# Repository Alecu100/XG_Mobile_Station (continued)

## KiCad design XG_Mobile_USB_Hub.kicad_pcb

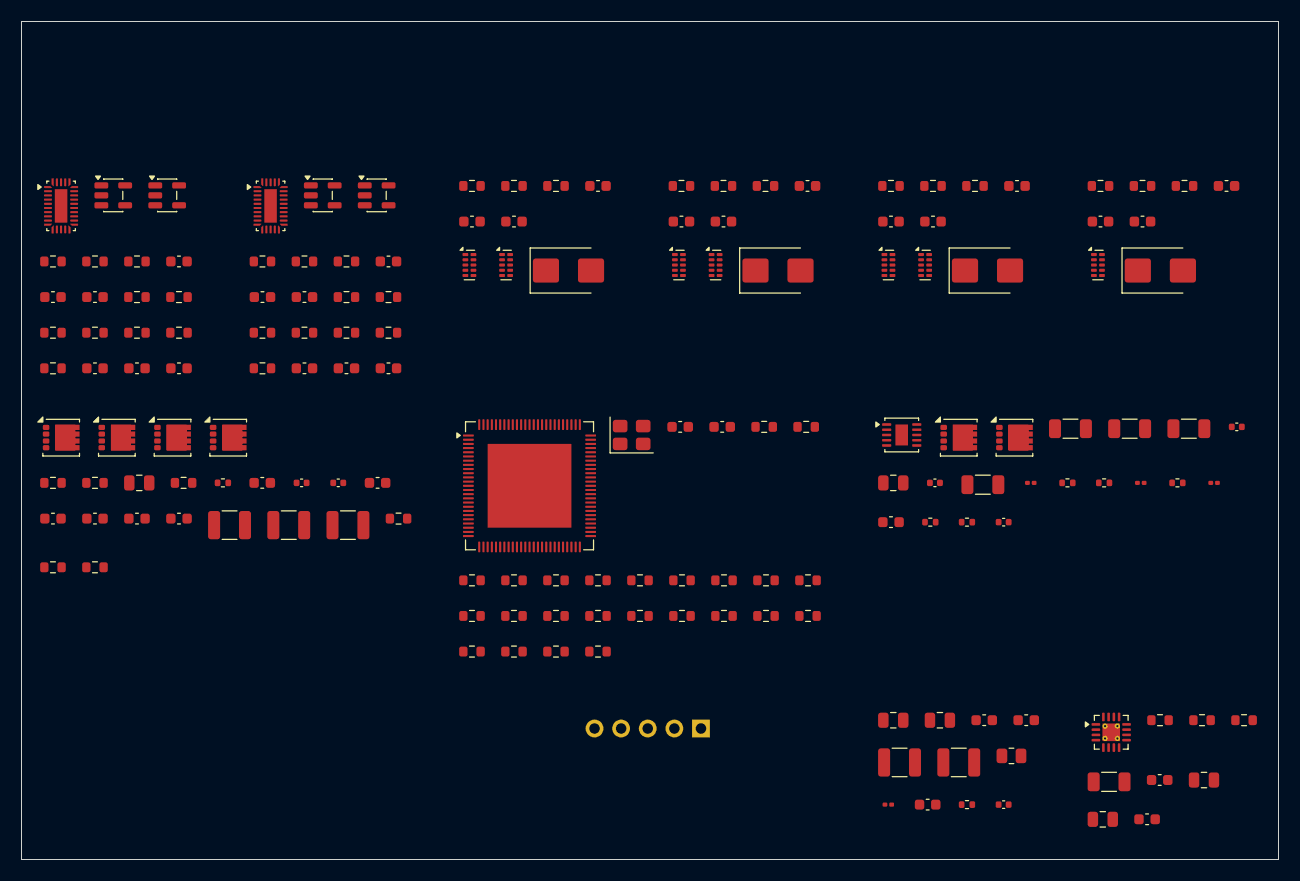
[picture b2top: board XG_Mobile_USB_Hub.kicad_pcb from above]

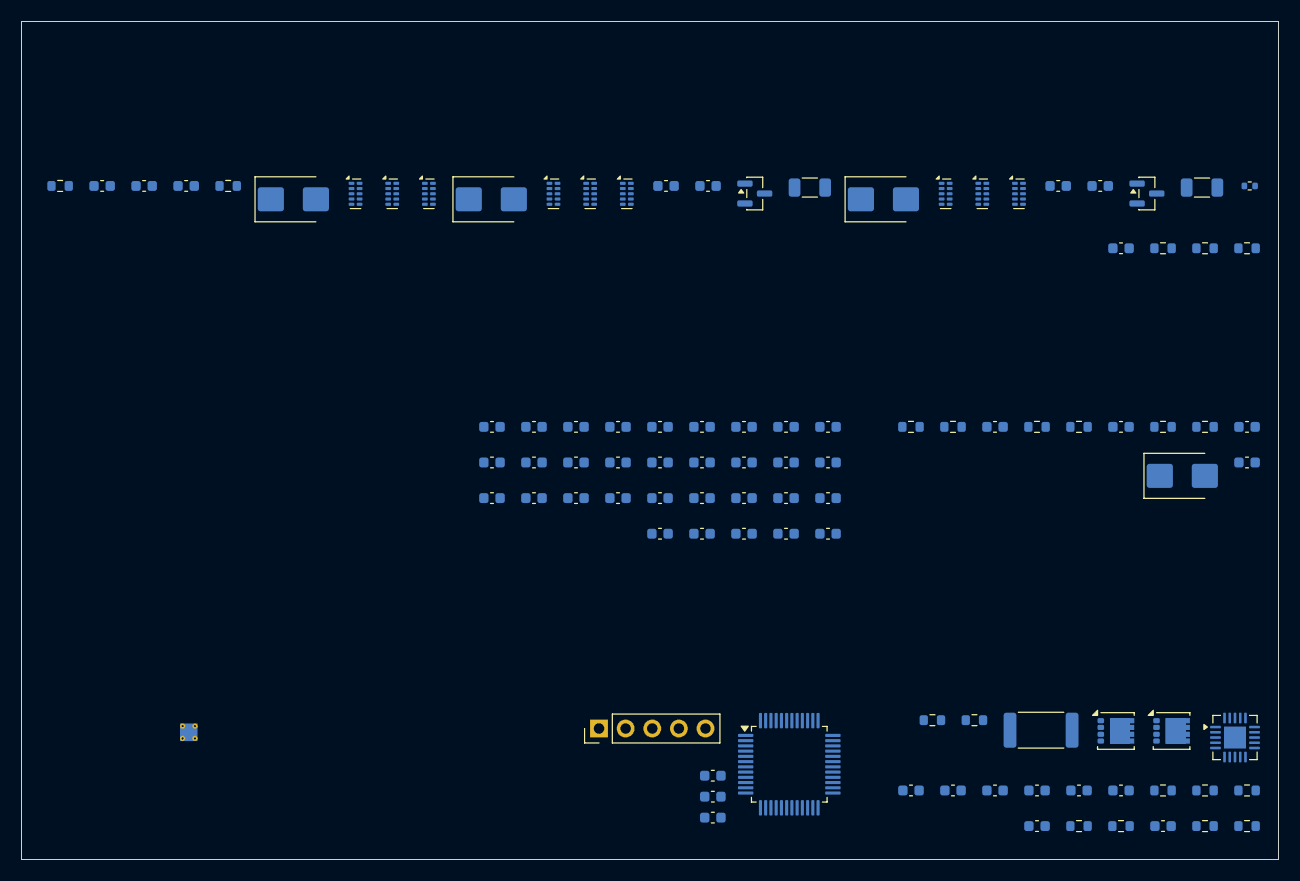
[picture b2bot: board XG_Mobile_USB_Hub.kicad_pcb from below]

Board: 4 copper layers, 120.0 x 80.0 mm, 300 parts (99 on the bottom side), 177 nets, no tracks yet.

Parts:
C101: 180pF; C_0805_2012Metric
C102: 120nF - REVIEW LOOP; C_0603_1608Metric
C103: 220pF - REVIEW LOOP; C_0402_1005Metric
C104: 33nF; C_0402_1005Metric
C105, C106: 22uF 6.3V; C_0603_1608Metric
C107, C108, C304: 100nF 16V; C_0603_1608Metric
C109, C303, C402, C1401: 100nF 25V; C_0603_1608Metric
C110: 10uF 25V; C_1210_3225Metric
C111: 27uF 25V; C111
C112: 120uF 35V; C112
C113: 120uF 35V; C113
C114, C115: 10uF 50V; C_1210_3225Metric
C201, C202, C203, C401: 10uF 25V; C_1206_3216Metric
C204: 1uF 25V; C_0402_1005Metric
C205: 2.2uF 10V; C_0805_2012Metric
C206: 100nF 16V; C_0402_1005Metric
C207: 100uF 10V; C_1206_3216Metric
C208: 3.3nF; C_0201_0603Metric
C209: 120pF; C_0201_0603Metric
C210: 4.3nF; C_0603_1608Metric
C211: 1nF; C_0402_1005Metric
C301, C302: 10uF 25V; C_0805_2012Metric
C305, C306: 15uF 16V; C_1210_3225Metric
C307: 150pF; C_0603_1608Metric
C308: 22nF; C_0402_1005Metric
C403, C404: 22uF 6.3V; C_0805_2012Metric
C405: 3.3nF; C_0603_1608Metric
C501, C502: 27pF C0G - tune CL; C_0603_1608Metric
C503, C504, C505, C506, C507, C508, C509, C510, C511, C512, C513, C514, C515, C516, C517, C518, C519, C520, C604, C605, C606, C607, C704, C705, C706, C707, C1206, C1300, C1301, C1304, C1306: 100nF; C_0603_1608Metric
C521, C522: 10uF 6.3V; C_0603_1608Metric
C523, C524, C525, C526, C527, C528, C529, C530, C531, C532, C533, C534: 220nF 10V; C_0603_1608Metric
C601, C701, C801, C901, C1001, C1101: 2.2nF; C_0603_1608Metric
C602, C702, C802, C902, C1002, C1102, C1205: 1uF 10V; C_0603_1608Metric
C603, C703, C803, C903, C1003, C1103: 10uF 10V; C_0603_1608Metric
C608, C708: 4.7uF 10V; C_0603_1608Metric
C804: 220uF 10V +/-20% low ESR; C804
C904: 220uF 10V +/-20% low ESR; C904
C1004: 220uF 10V +/-20% low ESR; C1004
C1104: 220uF 10V +/-20% low ESR; C1104
C1200: 100nF 50V; C_0603_1608Metric
C1201, C1202: 330pF 50V; C_0603_1608Metric
C1203: 2.2uF 50V; C_0603_1608Metric
C1204: 100nF 10V; C_0603_1608Metric
C1207, C1303, C1402, C1403, C1404: 1nF; C_0603_1608Metric
C1302: 4.7uF 6.3V; C_0603_1608Metric
C1305: 1uF 6.3V; C_0603_1608Metric
C1400: 100uF 25V polymer; C1400
D600, D601, D602, D700, D701, D702, D800, D801, D900, D901, D1000, D1001, D1100, D1200, D1201, D1202: TPD4E05U06DQA; USON-10_2.5x1.0mm_P0.5mm
D609, D709, D809, D909, D1009, D1109: SMBJ5.0CA; D_SMB
D1203: SMBJ22CA; D_SMB
D1400: SMBJ13CA; D_SMB
F1401: 12A >=32VDC; F1401
F1402: 12A >=32VDC; F1402
F1403: 25A >=32VDC; F1403
J600: USB-C 24-pin 5A / 10Gbps; J600
J700: USB-C 24-pin 5A / 10Gbps; J700
J800: USB3_A; J800
J900: USB3_A; J900
J1000: USB3_A; J1000
J1100: USB_A; J1100
J1200: USB-C 24-pin 5A / 10Gbps; J1200
J1300: SWD_5; PinHeader_1x05_P2.54mm_Vertical
J1401: GPU_8PIN; J1401
J1402: GPU_8PIN; J1402
J1403: EPS_8PIN; J1403
L101: 2.2uH 12.12A / Isat 18.18A; L101
L201: 800nH; L201
L301: 2.2uH; L301
L401: 2.2uH; L401
Q101, Q102, Q103, Q104, Q202, Q1200, Q1201: CSD17577Q3A; VSON-8_3.3x3.3mm_P0.65mm_NexFET
Q201: CSD17304Q3; VSON-8_3.3x3.3mm_P0.65mm_NexFET
Q600, Q700: 2N7002; SOT-23
R101: 2m 2W - REVIEW OCP; R101
R102, R103: 10; R_0603_1608Metric
R104: 51k; R_0603_1608Metric
R105: 4.75k - REVIEW LOOP; R_0402_1005Metric
R106, R403, R502, R507, R508, R509, R602, R604, R605, R608, R609, R702, R704, R705, R708, R709, R802, R902, R1002, R1102, R1203, R1300, R1401, R1403, R1405: 10k; R_0603_1608Metric
R107, R108, R510, R511, R512, R513, R514, R515, R516, R517, R518, R519, R520, R521, R522, R523, R524, R610, R710, R1204, R1205, R1206, R1207, R1400, R1402, R1404: 100k; R_0603_1608Metric
R201, R304: 100k; R_0402_1005Metric
R202: 7.5k; R_0402_1005Metric
R203, R302: 10k; R_0201_0603Metric
R204: 1.37k; R_0402_1005Metric
R205: 2.26k; R_0402_1005Metric
R206: 274; R_0402_1005Metric
R301: 45.3k; R_0805_2012Metric
R303: 52.3k; R_0402_1005Metric
R401: 43.7k 0.1%; R_0603_1608Metric
R402, R1208, R1303: 100k 0.1%; R_0603_1608Metric
R501: 12k 1%; R_0603_1608Metric
R503, R504, R505, R506, R606, R706: 200k; R_0603_1608Metric
R601, R701, R801, R901, R1001, R1101: 36.5k; R_0603_1608Metric
R603, R703: 1.02k 1%; R_0603_1608Metric
R607, R707: 900k; R_0603_1608Metric
R611, R711: 330 0.25W; R_1206_3216Metric
R803, R903, R1003: 3.01k 1%; R_0603_1608Metric
R1103: 5.11k 1%; R_0603_1608Metric
R1200: 7m 1W 1%; R_2512_6332Metric
R1201: 10k 1%; R_0603_1608Metric
R1202: 560 1%; R_0603_1608Metric
R1209, R1304: 10k 0.1%; R_0603_1608Metric
R1301, R1302: 4.7k; R_0603_1608Metric
SW1300: Reset_Button; SW1300
SW1400: SPDT 30A >=24VDC BBM; SW1400
U101: LM51772RHAR; U101
U201: TPS40305DRCR; VSON-10-1EP_3x3mm_P0.5mm_EP1.2x2mm
U301: TPS56A37RPAR; U301
U401: TPS62130; VQFN-16-1EP_3x3mm_P0.5mm_EP1.68x1.68mm_ThermalVias
U501: USB7206CT_KDX; VQFN-100-1EP_12x12mm_P0.4mm_EP8x8mm
U600, U700: HD3SS3220IRNHR; Texas_RNH0030A_WQFN-30-1EP_2.5x4.5mm_P0.4mm_EP1.2x3.2mm
U601: TPS259470LRPW; U601
U602, U702: 74LVC1G04; SOT-23-5
U603, U703: 74LVC1G08; SOT-23-5
U701: TPS259470LRPW; U701
U801: TPS259470LRPW; U801
U901: TPS259470LRPW; U901
U1001: TPS259470LRPW; U1001
U1101: TPS259470LRPW; U1101
U1200: TCPP03-M20; TQFN-20-1EP_4x4mm_P0.5mm_EP2.1x2.1mm
U1201: HD3SS3212IRKSR; U1201
U1300: STM32G071CBT6; LQFP-48_7x7mm_P0.5mm
Y501: 25MHz CL=18pF; Crystal_SMD_3225-4Pin_3.2x2.5mm

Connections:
3V3_FB: C307.2, R301.2, R302.1
3V3_PG: R304.2, U1300.48
5V_BOOT: C206.1, U201.6
5V_BP: C205.1, R201.1, U201.10
5V_COMP: C209.1, C210.1, U201.4
5V_COMP_MID: C210.2, R205.1
5V_FB: C209.2, C211.2, R203.2, R204.1, R205.2, U201.5
5V_FF_MID: C211.1, R206.2
5V_HG: Q201.4, U201.7
5V_LG: Q202.4, R202.1, U201.9
5V_PG: R201.2, U201.3
5V_SS: C208.1, U201.2
5V_SW: C206.2, Q201.1, Q201.2, Q201.3, Q202.5, U201.8
CORE_FB: R401.2, R402.1, U401.5
CORE_PG: R403.2, U401.4, U1300.47
CORE_SS: C405.1, U401.9
CORE_SW: U401.1, U401.2, U401.3
EPS_ADC: C1404.1, R1404.2, R1405.1, U1300.16
GND: C103.2, C104.2, C105.2, C106.2, C109.2, C110.2, C114.2, C115.2, C201.2, C202.2, C203.2, C204.2, C205.2, C207.2, C208.2, C301.2, C302.2, C303.2, C305.2, C306.2, C308.2, C401.2, C402.2, C403.2, C404.2, C405.2, C501.2, C502.2, C503.2, C504.2, C505.2, C506.2, C507.2, C508.2, C509.2, C510.2, C511.2, C512.2, C513.2, C514.2, C515.2, C516.2, C517.2, C518.2, C519.2, C520.2, C521.2, C522.2, C601.2, C602.2, C603.2, C604.2, C605.2, C606.2, C607.2, C608.2, C701.2, C702.2, C703.2, C704.2, C705.2, C706.2, C707.2, C708.2, C801.2, C802.2, C803.2, C901.2, C902.2, C903.2, C1001.2, C1002.2, C1003.2, C1101.2, C1102.2, C1103.2, C1200.2, C1201.2, C1202.2, C1203.2, C1204.2, C1205.2, C1206.2, C1207.2, C1300.2, C1301.2, C1302.2, C1303.2, C1304.2, C1305.2, C1306.2, C1401.2, C1402.2, C1403.2, C1404.2, D600.3, D600.8, D601.3, D601.8, D602.3, D602.8, D609.2, D700.3, D700.8, D701.3, D701.8, D702.3, D702.8, D709.2, D800.3, D800.8, D801.3, D801.8, D809.2, D900.3, D900.8, D901.3, D901.8, D909.2, D1000.3, D1000.8, D1001.3, D1001.8, D1009.2, D1100.3, D1100.8, D1109.2, D1200.3, D1200.8, D1201.3, D1201.8, D1202.3, D1202.8, D1203.2, D1400.2, J1300.5, Q102.1, Q102.2, Q102.3, Q104.1, Q104.2, Q104.3, Q202.1, Q202.2, Q202.3, Q600.2, Q700.2, R104.2, R105.2, R107.2, R108.2, R202.2, R204.2, R302.2, R303.2, R402.2, R501.2, R502.2, R503.2, R504.2, R505.2, R506.2, R510.2, R511.2, R512.2, R513.2, R514.2, R515.2, R516.2, R517.2, R518.2, R519.2, R520.2, R521.2, R522.2, R523.2, R524.2, R602.2, R603.2, R610.2, R702.2, R703.2, R710.2, R802.2, R803.2, R902.2, R903.2, R1002.2, R1003.2, R1102.2, R1103.2, R1202.2, R1204.2, R1207.2, R1209.2, R1304.2, R1401.2, R1403.2, R1405.2, U201.11, U401.6, U401.7, U401.8, U401.15, U401.16, U401.17, U501.24, U501.101, U600.12, U600.13, U600.28, U600.29, U600.31, U602.3, U603.3, U700.12, U700.13, U700.28, U700.29, U700.31, U702.3, U703.3, U1200.8, U1200.12, U1200.16, U1200.21, U1300.7, U1300.29, U1300.32, Y501.2, Y501.4
GPU1_ADC: C1402.1, R1400.2, R1401.1, U1300.14
GPU2_ADC: C1403.1, R1402.2, R1403.1, U1300.15
HUB_CFG_STRAP1: R502.1, U501.21
HUB_CFG_STRAP2: R503.1, U501.22
HUB_CFG_STRAP3: R504.1, U501.23
HUB_PF3: R510.1, U501.44
HUB_PF4: R511.1, U501.45
HUB_PF5: R512.1, U501.46
HUB_PF6: R513.1, U501.47
HUB_PF7: R514.1, U501.48
HUB_PF18: R515.1, U501.61
HUB_PF19: R516.1, U501.66
HUB_PF29: R522.1, U501.74
HUB_PF31: R517.1, U501.3
HUB_RBIAS: R501.1, U501.100
HUB_RESET_N: R523.1, U501.1, U1300.17
HUB_SPI_CE_N: R505.1, U501.69
HUB_SPI_CLK: R518.1, U501.68
HUB_SPI_D0: R506.1, U501.70
HUB_SPI_D1: R519.1, U501.71
HUB_SPI_D2: R520.1, U501.72
HUB_SPI_D3: R521.1, U501.73
HUB_TEST1: R507.1, U501.63
HUB_TEST2: R508.1, U501.64
HUB_TEST3: R509.1, U501.65
HUB_VBUS_DET: R524.1, U501.2, U1300.18
HUB_XTALI: C501.1, U501.98, Y501.1
HUB_XTALO: C502.1, U501.97, Y501.3
I2C_SCL: R1301.2, U501.75, U1200.18, U1300.45
I2C_SDA: R1302.2, U501.76, U1200.17, U1300.46
MCU_CC1: U1200.1, U1300.28
MCU_CC2: U1200.3, U1300.27
MCU_NRST: C1300.1, J1300.4, R1300.2, U1300.10
P1_ATTACHED: U602.4, U603.1
P1_CTL: U501.60, U603.2
P1_CURRENT: R604.2, U600.3
P1_DIR: R606.2, U600.11
P1_DISCH: Q600.3, R611.2
P1_DM: D602.2, U501.6
P1_DP: D602.1, U501.5
P1_EN: R610.1, U603.4
P1_ID_N: Q600.1, R608.2, U600.27, U602.2, U1300.33
P1_OVLO: R601.2, R602.1
P1_PORT: R605.2, U600.4
P1_RX1N: D600.5, U600.14
P1_RX1P: D600.4, U600.15
P1_RX2N: D601.5, U600.18
P1_RX2P: D601.4, U600.19
P1_RXN: U501.11, U600.10
P1_RXP: U501.10, U600.9
P1_TX1N: D600.2, U600.16
P1_TX1P: D600.1, U600.17
P1_TX2N: D601.2, U600.20
P1_TX2P: D601.1, U600.21
P1_TXN: C526.1, U501.8
P1_TXN_AC: C526.2, U600.7
P1_TXP: C525.1, U501.7
P1_TXP_AC: C525.2, U600.6
P1_VBUS: C603.1, D609.1, R607.1, R611.1
P1_VBUS_DET: R607.2, U600.5
P1_VCONN_FLT: R609.2, U600.24
P2_ATTACHED: U702.4, U703.1
P2_CTL: U501.59, U703.2
P2_CURRENT: R704.2, U700.3
P2_DIR: R706.2, U700.11
P2_DISCH: Q700.3, R711.2
P2_DM: D702.2, U501.15
P2_DP: D702.1, U501.14
P2_EN: R710.1, U703.4
P2_ID_N: Q700.1, R708.2, U700.27, U702.2, U1300.34
P2_OVLO: R701.2, R702.1
P2_PORT: R705.2, U700.4
P2_RX1N: D700.5, U700.14
P2_RX1P: D700.4, U700.15
P2_RX2N: D701.5, U700.18
P2_RX2P: D701.4, U700.19
P2_RXN: U501.20, U700.10
P2_RXP: U501.19, U700.9
P2_TX1N: D700.2, U700.16
P2_TX1P: D700.1, U700.17
P2_TX2N: D701.2, U700.20
P2_TX2P: D701.1, U700.21
P2_TXN: C528.1, U501.17
P2_TXN_AC: C528.2, U700.7
P2_TXP: C527.1, U501.16
P2_TXP_AC: C527.2, U700.6
P2_VBUS: C703.1, D709.1, R707.1, R711.1
P2_VBUS_DET: R707.2, U700.5
P2_VCONN_FLT: R709.2, U700.24
P3_DM: D800.2, U501.28
P3_DP: D800.1, U501.27
P3_OVLO: R801.2, R802.1
P3_RXN: D801.5, U501.33
P3_RXP: D801.4, U501.32
P3_TXN: C530.1, U501.30
P3_TXN_AC: C530.2, D801.2
P3_TXP: C529.1, U501.29
P3_TXP_AC: C529.2, D801.1
P3_VBUS: C803.1, D809.1
P4_DM: D900.2, U501.35
P4_DP: D900.1, U501.34
P4_OVLO: R901.2, R902.1
P4_RXN: D901.5, U501.40
P4_RXP: D901.4, U501.39
P4_TXN: C532.1, U501.37
P4_TXN_AC: C532.2, D901.2
P4_TXP: C531.1, U501.36
P4_TXP_AC: C531.2, D901.1
P4_VBUS: C903.1, D909.1
P5_DM: D1000.2, U501.82
P5_DP: D1000.1, U501.81
P5_OVLO: R1001.2, R1002.1
P5_RXN: D1001.5, U501.87
P5_RXP: D1001.4, U501.86
P5_TXN: C534.1, U501.84
P5_TXN_AC: C534.2, D1001.2
P5_TXP: C533.1, U501.83
P5_TXP_AC: C533.2, D1001.1
P5_VBUS: C1003.1, D1009.1
P6_DM: D1100.2, U501.41
P6_DP: D1100.1, U501.42
P6_OVLO: R1101.2, R1102.1
P6_VBUS: C1103.1, D1109.1
PD_COMP: C102.1, C103.1
PD_COMP_MID: C102.2, R105.1
PD_CSA: C101.1, R102.2
PD_CSB: C101.2, R103.2
PD_EN: R107.1, U1300.19
PD_IANA: U1200.4, U1300.12
PD_NFLT: R106.2, U1300.39
PD_NRST: R108.1, U1300.20
PD_RAW: C114.1, C115.1, Q103.5, Q1200.5, R1303.1
PD_RAW_ADC: C1303.1, R1303.2, R1304.1, U1300.13
PD_SW1: C107.2, Q101.1, Q101.2, Q101.3, Q102.5, R102.1
PD_SW2: C108.2, Q103.1, Q103.2, Q103.3, Q104.5
SWCLK: J1300.3, U1300.36
SWDIO: J1300.2, U1300.35
TCPP_EN: R1204.1, U1200.20, U1300.30
UP_ADC: C1207.1, R1208.2, R1209.1, U1300.11
UP_CBIAS: C1200.1, U1200.14
UP_CC1: C1201.1, U1200.15
UP_CC2: C1202.1, U1200.13
UP_DM: D1202.2, U501.90
UP_DP: D1202.1, U501.89
UP_FAULT_N: R1203.2, U1200.19, U1300.38
UP_FET_SOURCE: Q1200.1, Q1200.2, Q1200.3, Q1201.1, Q1201.2, Q1201.3, R1205.2, U1200.6
UP_GATE: Q1200.4, Q1201.4, R1205.1, U1200.5
UP_ISENSE: Q1201.5, R1200.1, U1200.10
UP_MUX_OEN: R1206.2, U1300.41
UP_MUX_SEL: R1207.1, U1300.40
UP_OVP: R1201.2, R1202.1, U1200.11
UP_TXN: C524.1, U501.92
UP_TXP: C523.1, U501.91
UP_VBUS: C1203.1, D1203.1, R1200.2, R1201.1, R1208.1, U1200.9
V3V3: C305.1, C306.1, C307.1, C512.1, C513.1, C514.1, C515.1, C516.1, C517.1, C518.1, C519.1, C520.1, C522.1, C605.1, C606.1, C607.1, C705.1, C706.1, C707.1, C1206.1, C1301.1, C1302.1, C1304.1, C1305.1, C1306.1, J1300.1, R106.1, R301.1, R304.1, R403.1, R507.2, R508.2, R509.2, R606.1, R608.1, R609.1, R706.1, R708.1, R709.1, R1203.1, R1206.1, R1300.1, R1301.1, R1302.1, U401.13, U501.26, U501.43, U501.53, U501.62, U501.67, U501.79, U501.88, U501.99, U600.8, U602.5, U603.5, U700.8, U702.5, U703.5, U1300.4, U1300.5, U1300.6
V5: C207.1, C602.1, C604.1, C608.1, C702.1, C704.1, C708.1, C802.1, C902.1, C1002.1, C1102.1, C1204.1, C1205.1, R203.1, R206.1, R601.1, R604.1, R605.1, R701.1, R704.1, R705.1, R801.1, R901.1, R1001.1, R1101.1, U600.30, U700.30, U1200.2
VCORE: C403.1, C404.1, C503.1, C504.1, C505.1, C506.1, C507.1, C508.1, C509.1, C510.1, C511.1, C521.1, R401.1, U401.14, U501.9, U501.18, U501.25, U501.31, U501.38, U501.55, U501.78, U501.85, U501.93
VIN12: C109.1, C110.1, C201.1, C202.1, C203.1, C204.1, C301.1, C302.1, C303.1, C401.1, C402.1, C1401.1, D1400.1, Q101.5, Q201.5, U201.1, U401.10, U401.11, U401.12

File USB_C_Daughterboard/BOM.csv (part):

Reference,Value,MPN,LCSC,Footprint,DNP,Sheet
J1401,GPU_8PIN,PCIe_GPU_8PIN_KEYED_HEADER_SELECTION_REQUIRED,,,False,Power
F1401,12A >=32VDC,FUSE_AND_HOLDER_SELECTION_REQUIRED,,,False,Power
J1402,GPU_8PIN,PCIe_GPU_8PIN_KEYED_HEADER_SELECTION_REQUIRED,,,False,Power
F1402,12A >=32VDC,FUSE_AND_HOLDER_SELECTION_REQUIRED,,,False,Power
J1403,EPS_8PIN,EPS_CPU_8PIN_KEYED_HEADER_SELECTION_REQUIRED,,,False,Power
F1403,25A >=32VDC,FUSE_AND_HOLDER_SELECTION_REQUIRED,,,False,Power
SW1400,SPDT 30A >=24VDC BBM,DC_POWER_SELECTOR_SELECTION_REQUIRED,,,False,Power
C1400,100uF 25V polymer,INPUT_BULK_CAP_SELECTION_REQUIRED,,,False,Power
C1401,100nF 25V,SELECTION_REQUIRED,,Capacitor_SMD:C_0603_1608Metric,False,Power
R1400,100k,SELECTION_REQUIRED,,Resistor_SMD:R_0603_1608Metric,False,Power
R1401,10k,SELECTION_REQUIRED,,Resistor_SMD:R_0603_1608Metric,False,Power
C1402,1nF,SELECTION_REQUIRED,,Capacitor_SMD:C_0603_1608Metric,False,Power
R1402,100k,SELECTION_REQUIRED,,Resistor_SMD:R_0603_1608Metric,False,Power
R1403,10k,SELECTION_REQUIRED,,Resistor_SMD:R_0603_1608Metric,False,Power
C1403,1nF,SELECTION_REQUIRED,,Capacitor_SMD:C_0603_1608Metric,False,Power
R1404,100k,SELECTION_REQUIRED,,Resistor_SMD:R_0603_1608Metric,False,Power
R1405,10k,SELECTION_REQUIRED,,Resistor_SMD:R_0603_1608Metric,False,Power
C1404,1nF,SELECTION_REQUIRED,,Capacitor_SMD:C_0603_1608Metric,False,Power
D1400,SMBJ13CA,SMBJ13CA,,Diode_SMD:D_SMB,False,Power
U101,LM51772RHAR,LM51772RHAR,C41383743,,False,Power
Q101,CSD17577Q3A,CSD17577Q3A,,Package_SON:VSON-8_3.3x3.3mm_P0.65mm_NexFET,False,Power
Q102,CSD17577Q3A,CSD17577Q3A,,Package_SON:VSON-8_3.3x3.3mm_P0.65mm_NexFET,False,Power
Q103,CSD17577Q3A,CSD17577Q3A,,Package_SON:VSON-8_3.3x3.3mm_P0.65mm_NexFET,False,Power
Q104,CSD17577Q3A,CSD17577Q3A,,Package_SON:VSON-8_3.3x3.3mm_P0.65mm_NexFET,False,Power
R101,2m 2W - REVIEW OCP,WSR22L000FEA,,,False,Power
L101,2.2uH 12.12A / Isat 18.18A,APS1040M2R2A,C47327242,,False,Power
R102,10,CRCW060310R0FKEA,,Resistor_SMD:R_0603_1608Metric,False,Power
R103,10,CRCW060310R0FKEA,,Resistor_SMD:R_0603_1608Metric,False,Power
C101,180pF,C0805C181K5GACTU,,Capacitor_SMD:C_0805_2012Metric,False,Power
R104,51k,RC0603FR-0751KL,,Resistor_SMD:R_0603_1608Metric,False,Power
R105,4.75k - REVIEW LOOP,CRCW04024K75FKED,,Resistor_SMD:R_0402_1005Metric,False,Power
C102,120nF - REVIEW LOOP,GRM188R71C124KA01D,,Capacitor_SMD:C_0603_1608Metric,False,Power
C103,220pF - REVIEW LOOP,CC0402JRNPO8BN221,,Capacitor_SMD:C_0402_1005Metric,False,Power
C104,33nF,GRM155R61C333KA01D,,Capacitor_SMD:C_0402_1005Metric,False,Power
C105,22uF 6.3V,GRM188R60J226MEA0D,,Capacitor_SMD:C_0603_1608Metric,False,Power
C106,22uF 6.3V,GRM188R60J226MEA0D,,Capacitor_SMD:C_0603_1608Metric,False,Power
C107,100nF 16V,EMK107B7104KA-T,,Capacitor_SMD:C_0603_1608Metric,False,Power
C108,100nF 16V,EMK107B7104KA-T,,Capacitor_SMD:C_0603_1608Metric,False,Power
C109,100nF 25V,SELECTION_REQUIRED,,Capacitor_SMD:C_0603_1608Metric,False,Power
C110,10uF 25V,MSAST32NSB5106KTNA01,,Capacitor_SMD:C_1210_3225Metric,False,Power
C111,27uF 25V,25SVPF27MX,,,False,Power
C112,120uF 35V,35SVPF120M,,,False,Power
C113,120uF 35V,35SVPF120M,,,False,Power
C114,10uF 50V,C3225X7R1H106M250AC,,Capacitor_SMD:C_1210_3225Metric,False,Power
C115,10uF 50V,C3225X7R1H106M250AC,,Capacitor_SMD:C_1210_3225Metric,False,Power
R106,10k,SELECTION_REQUIRED,,Resistor_SMD:R_0603_1608Metric,False,Power
R107,100k,SELECTION_REQUIRED,,Resistor_SMD:R_0603_1608Metric,False,Power
R108,100k,SELECTION_REQUIRED,,Resistor_SMD:R_0603_1608Metric,False,Power
U201,TPS40305DRCR,TPS40305DRCR,,Package_SON:VSON-10-1EP_3x3mm_P0.5mm_EP1.2x2mm,False,Power
Q201,CSD17304Q3,CSD17304Q3,,Package_SON:VSON-8_3.3x3.3mm_P0.65mm_NexFET,False,Power
Q202,CSD17577Q3A,CSD17577Q3A,,Package_SON:VSON-8_3.3x3.3mm_P0.65mm_NexFET,False,Power
L201,800nH,XAL7070-801MEB,,,False,Power
C201,10uF 25V,GRM31CR71E106KA12L,,Capacitor_SMD:C_1206_3216Metric,False,Power
C202,10uF 25V,GRM31CR71E106KA12L,,Capacitor_SMD:C_1206_3216Metric,False,Power
C203,10uF 25V,GRM31CR71E106KA12L,,Capacitor_SMD:C_1206_3216Metric,False,Power
C204,1uF 25V,C1005X5R1E105K050BC,,Capacitor_SMD:C_0402_1005Metric,False,Power
C205,2.2uF 10V,GRM21BR71A225KA01L,,Capacitor_SMD:C_0805_2012Metric,False,Power
C206,100nF 16V,GRM155R71C104KA88D,,Capacitor_SMD:C_0402_1005Metric,False,Power
C207,100uF 10V,C3216X5R1A107M160AC,,Capacitor_SMD:C_1206_3216Metric,False,Power
C208,3.3nF,GRM033R71A332KA01D,,Capacitor_SMD:C_0201_0603Metric,False,Power
R201,100k,CRCW0402100KFKED,,Resistor_SMD:R_0402_1005Metric,False,Power
R202,7.5k,CRCW04027K50FKED,,Resistor_SMD:R_0402_1005Metric,False,Power
R203,10k,RC0201FR-0710KL,,Resistor_SMD:R_0201_0603Metric,False,Power
R204,1.37k,CRCW04021K37FKED,,Resistor_SMD:R_0402_1005Metric,False,Power
C209,120pF,GRM0335C1H121JA01D,,Capacitor_SMD:C_0201_0603Metric,False,Power
C210,4.3nF,C0603C432J5GAC7867,,Capacitor_SMD:C_0603_1608Metric,False,Power
R205,2.26k,CRCW04022K26FKED,,Resistor_SMD:R_0402_1005Metric,False,Power
R206,274,CRCW0402274RFKED,,Resistor_SMD:R_0402_1005Metric,False,Power
C211,1nF,GRM1555C1H102JA01J,,Capacitor_SMD:C_0402_1005Metric,False,Power
U301,TPS56A37RPAR,TPS56A37RPAR,,,False,Power
L301,2.2uH,VLP8040T-2R2N,,,False,Power
C301,10uF 25V,MSAST21GBB5106MTNA01,,Capacitor_SMD:C_0805_2012Metric,False,Power
C302,10uF 25V,MSAST21GBB5106MTNA01,,Capacitor_SMD:C_0805_2012Metric,False,Power
C303,100nF 25V,C0603C104M3VACTU,,Capacitor_SMD:C_0603_1608Metric,False,Power
C304,100nF 16V,EMK107B7104KA-T,,Capacitor_SMD:C_0603_1608Metric,False,Power
C305,15uF 16V,C3225X5R1C156M250AA,,Capacitor_SMD:C_1210_3225Metric,False,Power
C306,15uF 16V,C3225X5R1C156M250AA,,Capacitor_SMD:C_1210_3225Metric,False,Power
R301,45.3k,CRCW080545K3FKEA,,Resistor_SMD:R_0805_2012Metric,False,Power
R302,10k,RC0201FR-0710KL,,Resistor_SMD:R_0201_0603Metric,False,Power
C307,150pF,C0603C151K3GACTU,,Capacitor_SMD:C_0603_1608Metric,False,Power
R303,52.3k,CRCW040252K3FKED,,Resistor_SMD:R_0402_1005Metric,False,Power
C308,22nF,GRM155R71C223KA01D,,Capacitor_SMD:C_0402_1005Metric,False,Power
R304,100k,CRCW0402100KFKED,,Resistor_SMD:R_0402_1005Metric,False,Power
U401,TPS62130,TPS62130,,Package_DFN_QFN:VQFN-16-1EP_3x3mm_P0.5mm_EP1.68x1.68mm_ThermalVias,False,Power
L401,2.2uH,XAL5030-222MEC,,,False,Power
R401,43.7k 0.1%,SELECTION_REQUIRED,,Resistor_SMD:R_0603_1608Metric,False,Power
R402,100k 0.1%,SELECTION_REQUIRED,,Resistor_SMD:R_0603_1608Metric,False,Power
R403,10k,SELECTION_REQUIRED,,Resistor_SMD:R_0603_1608Metric,False,Power
C401,10uF 25V,GRM31CR71E106KA12L,,Capacitor_SMD:C_1206_3216Metric,False,Power
C402,100nF 25V,SELECTION_REQUIRED,,Capacitor_SMD:C_0603_1608Metric,False,Power
C403,22uF 6.3V,GRM21BR60J226ME39L,,Capacitor_SMD:C_0805_2012Metric,False,Power
C404,22uF 6.3V,GRM21BR60J226ME39L,,Capacitor_SMD:C_0805_2012Metric,False,Power
C405,3.3nF,SELECTION_REQUIRED,,Capacitor_SMD:C_0603_1608Metric,False,Power
U1300,STM32G071KBT6N,STM32G071KBT6N,,Package_QFP:LQFP-32_7x7mm_P0.8mm,False,MCU
J1300,SWD_5,SWD 1x5 2.54mm,,Connector_PinHeader_2.54mm:PinHeader_1x05_P2.54mm_Vertical,False,MCU
SW1300,Reset_Button,RESET_SWITCH_SELECTION_REQUIRED,,,False,MCU
R1300,10k,SELECTION_REQUIRED,,Resistor_SMD:R_0603_1608Metric,False,MCU
C1300,100nF,SELECTION_REQUIRED,,Capacitor_SMD:C_0603_1608Metric,False,MCU
C1301,100nF,SELECTION_REQUIRED,,Capacitor_SMD:C_0603_1608Metric,False,MCU
C1302,4.7uF 6.3V,SELECTION_REQUIRED,,Capacitor_SMD:C_0603_1608Metric,False,MCU
R1301,4.7k,SELECTION_REQUIRED,,Resistor_SMD:R_0603_1608Metric,False,MCU
R1302,4.7k,SELECTION_REQUIRED,,Resistor_SMD:R_0603_1608Metric,False,MCU
R1303,100k 0.1%,SELECTION_REQUIRED,,Resistor_SMD:R_0603_1608Metric,False,MCU
R1304,10k 0.1%,SELECTION_REQUIRED,,Resistor_SMD:R_0603_1608Metric,False,MCU
C1303,1nF,SELECTION_REQUIRED,,Capacitor_SMD:C_0603_1608Metric,False,MCU
J1200,USB-C 24-pin 5A / 10Gbps,CONNECTOR_SELECTION_REQUIRED,,,False,MCU
U1200,TCPP03-M20,TCPP03-M20,C3662955,Package_DFN_QFN:TQFN-20-1EP_4x4mm_P0.5mm_EP2.1x2.1mm,False,MCU
Q1200,CSD17577Q3A,CSD17577Q3A,,Package_SON:VSON-8_3.3x3.3mm_P0.65mm_NexFET,False,MCU
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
